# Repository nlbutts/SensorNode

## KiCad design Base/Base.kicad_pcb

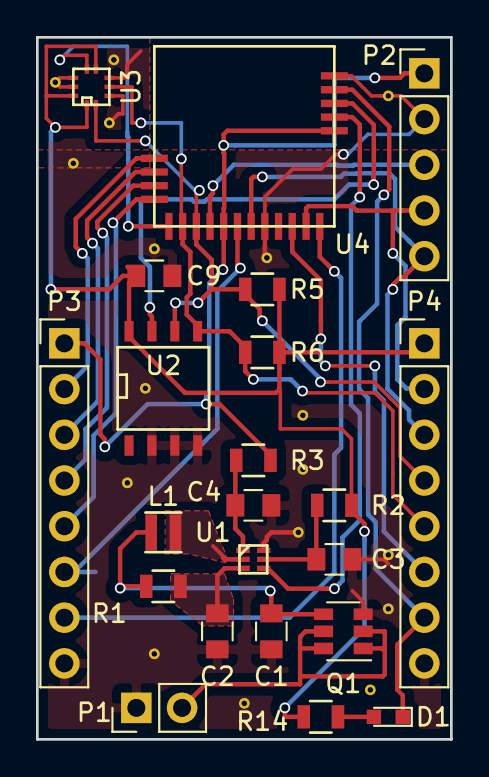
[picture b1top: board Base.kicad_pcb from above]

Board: 2 copper layers, 23.0 x 39.0 mm, 22 parts (0 on the bottom side), 26 nets.

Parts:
C1, C3, C4: 10u; C_0805
C2, C9: 0.1u; C_0805
D1: LED; LED_0603
L1: 4.7u; Inductor_Taiyo-Yuden_MD-2020
P1: CONN_01X02; Socket_Strip_Straight_1x02_Pitch2.54mm
P2: CONN_01X05; Socket_Strip_Straight_1x05_Pitch2.54mm
P3, P4: CONN_01X08; Socket_Strip_Straight_1x08_Pitch2.54mm
Q1: FDC606P; SOT-23-6
R1: 400; R_0805
R2, R3: 0; R_0805
R5, R6: 4k; R_0805
R14: 330; R_0805
U1: tps610981; WSON-6
U2: M24M01; SOIC-8-N
U3: LPS22HB; HLGA-10L
U4: CYBLE-022001-00; CYBLE-022001

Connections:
+BATT: C1.1, L1.1, Q1.4, R1.1
/ANALOG1: P3.3, U4.20
/ANALOG2: P4.6, U4.8
/GPIO1: P3.2, U4.21
/INT_DRDY: U3.7, U4.17
/LED: D1.1, P4.7, U4.2
/PS_MODE: U1.4, U4.4
/RX/MOSI: P3.5, U4.18
/SCL: P4.4, R5.2, U2.6, U3.2, U4.15
/SCLK: P3.6, U4.12
/SDA: P4.5, R6.2, U2.5, U3.4, U4.16
/SS: P3.7, U4.6
/SWDCLK: P2.4, P4.2, U4.7
/SWDIO: P2.5, P4.3, U4.11
/TX/MISO: P3.4, U4.19
/WP: U2.7, U4.3
/XRES: P2.3, U4.14
GND: C1.2, C2.2, C3.2, C4.2, C9.2, P1.1, P2.2, P3.8, P4.8, Q1.3, U1.6, U2.2, U2.3, U2.4, U3.3, U3.5, U3.8, U3.9, U4.1, U4.10
unnamed: C2.1, R1.2, U1.3
unnamed: C3.1, R2.2, U1.5
unnamed: C4.1, R3.2, U1.1
unnamed: D1.2, R14.1
unnamed: L1.2, U1.2
unnamed: P1.2, Q1.1, Q1.2, Q1.5, Q1.6
VCC: P2.1, P3.1, R3.1, U4.5, U4.13
VDD: C9.1, P4.1, R2.1, R5.1, R6.1, R14.2, U2.8, U3.1, U3.6, U3.10

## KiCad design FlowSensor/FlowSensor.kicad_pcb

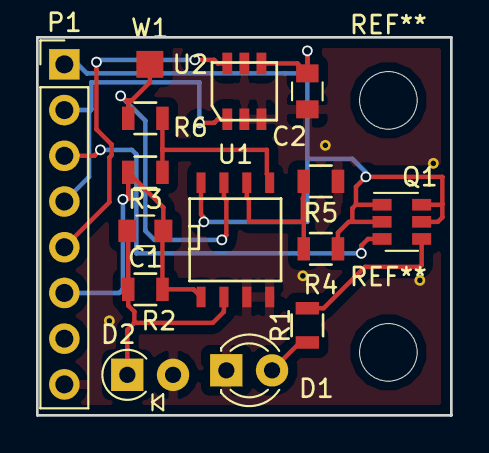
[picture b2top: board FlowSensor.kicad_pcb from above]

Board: 2 copper layers, 23.0 x 21.0 mm, 15 parts (0 on the bottom side), 12 nets.

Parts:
C1: 3p; C_0805
C2: 100n; C_0805
D1: LED; LED_D3.0mm_FlatTop
D2: PD15-21B/TR8; D_A-405_P2.54mm_Vertical_AnodeUp
P1: CONN_01X08; Socket_Strip_Straight_1x08_Pitch2.54mm
Q1: FDC606P; SOT-23-6
R1: 100; R_0805
R2: 1M; R_0805
R3: 6K; R_0805
R4, R5: 100k; R_0805
R6: 100K; R_0805
U1: LMC6062; SOIC-8-N
U2: TLV493D-A1B6; PG-TSOP-6-6-5
W1: TEST_1P; Measurement_Point_Square-SMD-Pad_Small

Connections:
/ANALOG1: C1.1, P1.6, R2.1, R3.2, U1.1
/GPIO1: P1.2, P1.4, U2.1
/GPIO2: P1.3, Q1.3
/SDA: P1.5, U2.6
GND: C2.2, D1.1, D2.2, P1.8, R5.1, U1.3, U1.4, U2.2, U2.3, U2.5
unnamed: C1.2, D2.1, R2.2, U1.2
unnamed: D1.2, R1.2
unnamed: Q1.4, R1.1
unnamed: R3.1, R6.2, U1.5
unnamed: R4.1, R5.2, U1.6
unnamed: R6.1, U1.7, W1.1
VDD: C2.1, P1.1, Q1.1, Q1.2, Q1.5, Q1.6, R4.2, U1.8, U2.4

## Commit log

2017-02-09 Initial checkin.
2017-02-09 Was able to generate the FlowSensor netlist and imported into the PCB, but the Base board fails.
2017-02-09 Got the bug fixed with the layout.
2017-02-13 Working on the layout for the base station.
2017-02-14 Completed the routing.
2017-02-15 Changing from a thermister ST LPS22HB pressure sensor.
2017-02-16 Added the software.
2017-02-17 Finished layout of SensorNode and FlowMeter boards.
2017-02-20 Ordered the PCBs
2017-03-28 Updates to the software and design.
